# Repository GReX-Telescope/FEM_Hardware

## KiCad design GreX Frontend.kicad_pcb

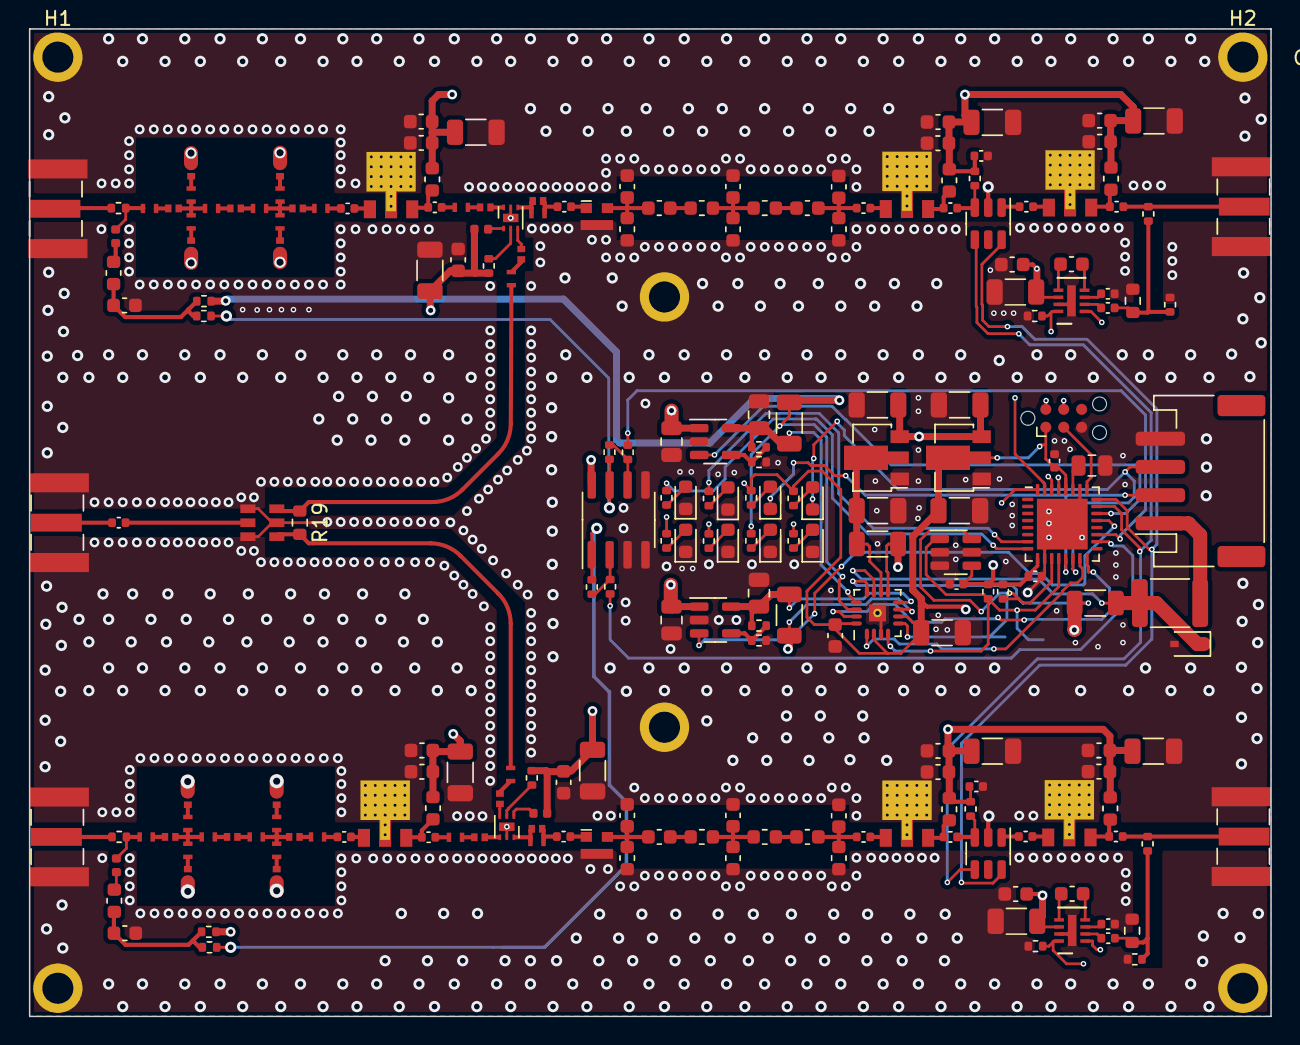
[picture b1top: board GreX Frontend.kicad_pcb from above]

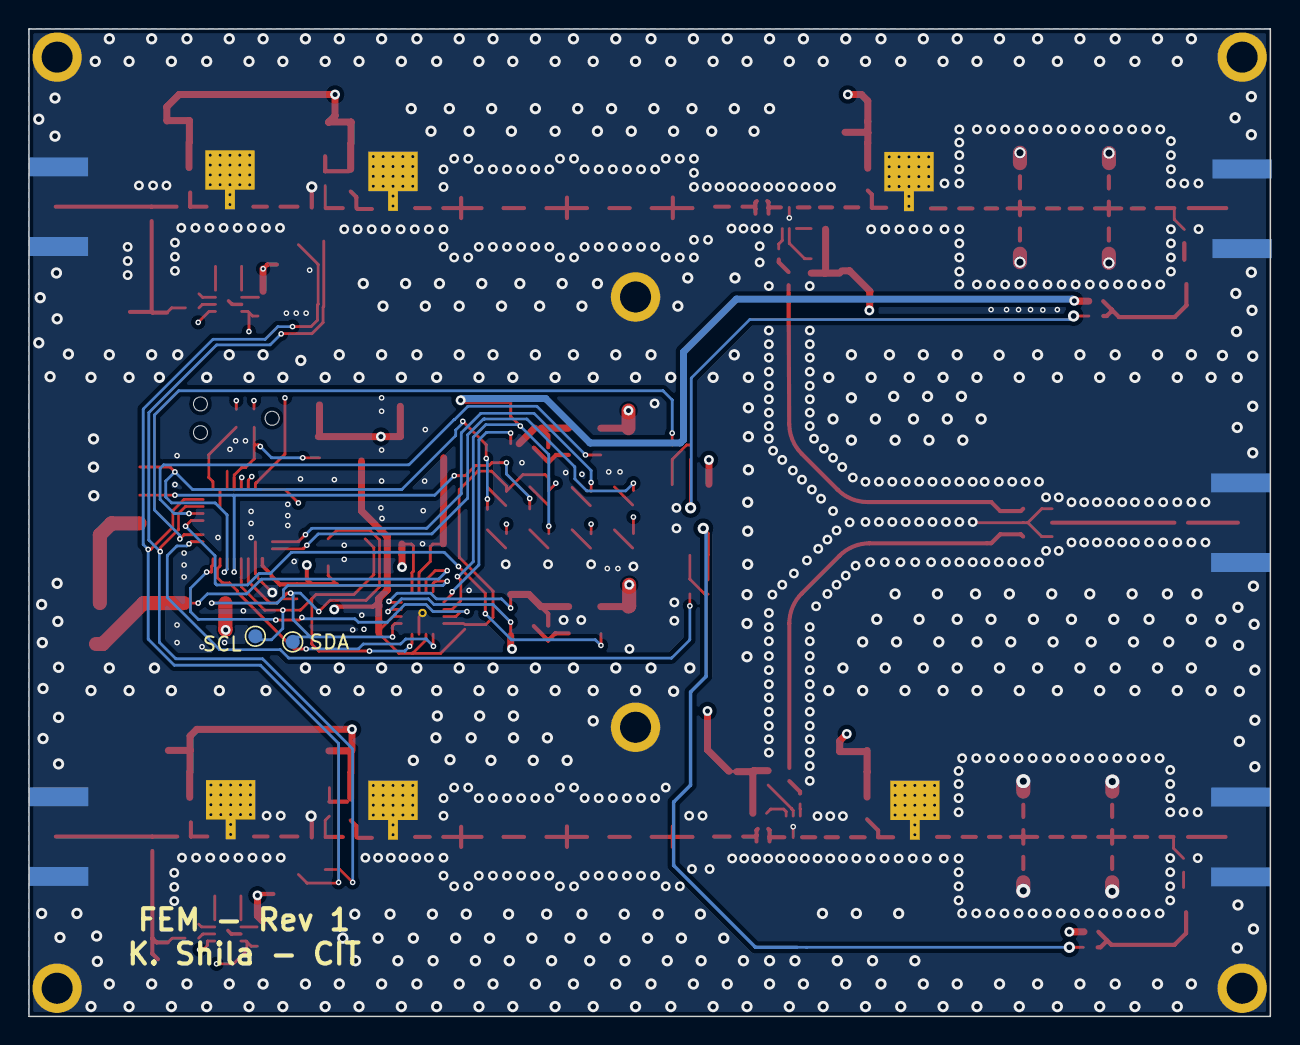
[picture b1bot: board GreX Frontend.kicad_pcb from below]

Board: 4 copper layers, 88.0 x 70.0 mm, 228 parts (2 on the bottom side), 137 nets.

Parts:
C1, C3, C15, C20, C36, C38, C43, C48: 100p; C_0603_1608Metric
C2, C16, C19, C34, C35, C44, C47, C49, C54, C63, C66: 100n; C_0402_1005Metric
C4, C7, C37, C39, C42, C56, C57, C59, C68, C69, C95, C96, C99: 100p; C_0402_1005Metric
C5, C17, C22, C32, C40, C45, C51, C52, C64, C93, C98: 1n; C_0603_1608Metric
C6, C18, C21, C25, C26, C27, C28, C31, C41, C46, C50, C53, C65, C94, C97: 10u; C_1206_3216Metric
C8, C14, C75, C81: 0.9p; C_0402_MDLX
C9, C12, C76, C79: 0.43p; C_0402_MDLX
C10, C13, C77, C80: 4.3p; C_0402_MDLX
C11, C78: 0.25p; C_0402_MDLX
C23, C24, C29, C30, C33: 1u; C_0805_2012Metric
C55, C67: 33n; C_0603_1608Metric
C70, C74, C82, C86: 18p; C_0603_1608Metric
C71, C73, C83, C85: 4.3p; C_0603_1608Metric
C72, C84: 33p; C_0603_1608Metric
C87, C88: 33p; C_0402_MDLX
C89, C90, C91, C92: 3.3p; C_0402_MDLX
D1, D2, D3, D4: RED; LED_0603_1608Metric
D5, D6: GREEN; LED_0603_1608Metric
D7, D8: BLUE; LED_0603_1608Metric
D9: D_Schottky; D_SOD-323
F1: Polyfuse; Fuse_1812_4532Metric
FB1, FB2: FerriteBead_Small; L_0603_1608Metric
H1, H2, H3, H4, H5, H6: MountingHole_2.2mm_M2_ISO7380_Pad
J1, J2, J5, J6, J7: Conn_Coaxial; SMA_Samtec_SMA-J-P-X-ST-EM1_EdgeMount
J3: Screw_Terminal_01x04; JST_PH_S4B-PH-SM4-TB_1x04-1MP_P2.00mm_Horizontal
J4: PROG; Tag-Connect_TC2030-IDC-NL_2x03_P1.27mm_Vertical
L2, L7: 82n; L_0402_1005Metric
L3, L8: 100n; L_0603_1608Metric
L4, L17, L25, L32: 9.9n; L_0402_MDLX
L5, L15, L26, L30: 8.2n; L_0402_MDLX
L9, L10, L18, L19: 1000n; L_0603_1608Metric
L12, L16, L27, L31: 7.1n; L_0402_MDLX
L13, L14, L28, L29: 16n; L_0402_MDLX
L20, L24, L33, L37: 9.1n; L_0603_1608Metric
L21, L23, L34, L36: 43n; L_0603_1608Metric
L22, L35: 5.6n; L_0603_1608Metric
L38, L39: 5.6n; L_0402_MDLX
L40, L41: 4.3n; L_0402_MDLX
L42, L43: 4.7n; L_0402_MDLX
L44, L45: 33n; L_0402_1005Metric
R1, R16, R26, R27, R28, R29: 0; R_0402_1005Metric
R2, R17: 33k; R_0402_1005Metric
R3, R18: 49.9; R_0603_1608Metric
R4, R5: 0.1; R_1206_3216Metric
R6, R7: 0.5; R_1206_3216Metric
R8, R9, R10, R11, R12, R13, R14, R15, R20, R21: 1k; R_0402_1005Metric
R19: 100; R_0603_1608Metric
R22, R23: 10k; R_0402_1005Metric
R24, R25: 20k; R_0402_1005Metric
R30, R32: 42.2k; R_0402_1005Metric
R31, R33: 12.4k; R_0402_1005Metric
R34, R35, R40, R41: 4.7k; R_0402_1005Metric
R36, R38: 226; R_0402_1005Metric
R37, R39: 61.9; R_0402_1005Metric
TP1, TP2: TestPoint; TestPoint_Pad_D1.0mm
U1, U5, U7, U15, U18, U20: ADL5545
U2, U3: GRF7001; DFN6-1.5mm-EP0.6x1.1
U4, U17: PAT1220-C-3DB; RF_Attenuator_Susumu_PAT1220
U6, U19: HMC291SE; SOT-23-6
U8, U21: LT5537; DFN-8-1EP_2x3mm_P0.5mm_EP0.61x2.2mm
U9: AZ1117-3.3; SOT-89-3
U10: AZ1117-5.0; SOT-89-3
U11, U12: SPX5205M5-L; SOT-23-5
U13: PAC1944; QFN-16_EP_3x3_Pitch0.5mm
U14: ATSAMD21E17L-M; QFN-32-1EP_5x5mm_P0.5mm_EP3.6x3.6mm
U16: TMP100; SOT-23-6
U24: SCN-2-11; FV1206-1
U25: RC4558; SOIC-8_3.9x4.9mm_P1.27mm

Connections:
+3V3: C2.1, C27.2, C31.2, C32.2, C34.1, C35.1, J4.1, R8.1, R14.1, R15.1, R34.1, R35.1, U9.2 (VO), U13.2 (Vdd), U13.6 (ADRSEL), U13.16 (~PWRDN), U14.9 (VDDIO/VDDANA), U14.28 (VDDIO), U16.4 (V+)
/RF/Input Stage 1/32_kHz: R20.2, R27.1, U25.7
/RF/Input Stage 1/Image Reject Filter1/1: L2.1, L4.1, R1.2
/RF/Input Stage 1/Image Reject Filter1/2: C4.1, L17.2
/RF/Input Stage 1/OUT: C7.2, L40.1
/RF/Input Stage 2/32_kHz: R21.2, R29.1, U25.1
/RF/Input Stage 2/Image Reject Filter1/1: L7.1, L25.1, R16.2
/RF/Input Stage 2/Image Reject Filter1/2: C39.1, L32.2
/RF/Input Stage 2/OUT: C42.2, L41.1
/RF/Output Stage 1/IF Filter1/In: C70.2, C71.2, L20.1, U4.2
/RF/Output Stage 1/IF Filter1/Out: C16.1, C73.1, C74.2, L24.1
/RF/Output Stage 1/In: C95.2, U4.1
/RF/Output Stage 2/IF Filter1/In: C82.2, C83.2, L33.1, U17.2
/RF/Output Stage 2/IF Filter1/Out: C44.1, C85.1, C86.2, L37.1
/RF/Output Stage 2/In: C96.2, U17.1
ALERT1: U13.1 (~ALERT), U14.15 (PA14)
ALERT2: U13.15 (~ALERT2), U14.16 (PA15)
ATTEN_V1: U6.4 (V1), U14.23 (PA24), U19.4 (V1)
ATTEN_V2: U6.6 (V2), U14.24 (PA25), U19.6 (V2)
GND: C1.1, C2.2, C3.1, C5.1, C6.1, C9.2, C10.1, C12.2, C13.1, C15.1, C17.1, C18.1, C20.1, C21.1, C22.1, C23.2, C24.2, C25.1, C26.1, C27.1, C28.1, C29.2, C30.2, C31.1, C32.1, C33.2, C34.2, C35.2, C36.1, C37.2, C38.1, C40.1, C41.1, C43.1, C45.1, C46.1, C48.1, C50.1, C51.1, C52.1, C53.1, C57.2, C64.1, C65.1, C69.2, C70.1, C72.1, C74.1, C76.2, C77.1, C79.2, C80.1, C82.1, C84.1, C86.1, C93.1, C94.1, C97.1, C98.1, C99.2, D1.1 (K), D2.1 (K), D3.1 (K), D4.1 (K), D5.1 (K), D6.1 (K), D9.2 (A), H1.1, H2.1, H3.1, H4.1, H5.1, H6.1, J1.2 (Ext), J2.2 (Ext), J3.4, J4.5, J5.2 (Ext), J6.2 (Ext), J7.2 (Ext), L20.2, L22.2, L24.2, L33.2, L35.2, L37.2, R2.2, R3.1, R17.2, R18.1, R31.2, R33.2, R37.2, R39.2, U1.2 (GND), U2.5 (GND), U2.EP (GND), U3.5 (GND), U3.EP (GND), U4.3, U5.2 (GND), U6.2 (GND), U7.2 (GND), U8.7 (GND), U8.9 (EP), U9.1 (GND), U10.1 (GND), U11.2 (GND), U12.2 (GND), U13.3 (GND), U13.17 (EP), U14.10 (GND), U14.26 (GND), U14.33 (EP), U15.2 (GND), U16.2 (GND), U16.3 (ADD1), U16.5 (ADD0), U17.3, U18.2 (GND), U19.2 (GND), U20.2 (GND), U21.7 (GND), U21.9 (EP), U24.1 (GND), U24.3 (GND), U24.5 (GND), U25.3 (+), U25.4 (V-), U25.5 (+)
unnamed: C1.2, FB1.2, R26.2, R27.2
unnamed: C4.2, U1.1
unnamed: C7.1, L3.2, U1.3
unnamed: C8.1, L4.2
unnamed: C8.2, L5.1, L12.2, L13.1
unnamed: C9.1, L5.2
unnamed: C10.2, L12.1
unnamed: C11.1, L13.2
unnamed: C11.2, L14.1
unnamed: C12.1, L15.2
unnamed: C13.2, L16.1
unnamed: C14.1, L14.2, L15.1, L16.2
unnamed: C14.2, L17.1
unnamed: C16.2, U5.1
unnamed: C19.1, L18.2, U5.3
unnamed: C19.2, R40.2, U6.3 (RF1)
unnamed: C33.1, U14.27 (VDDCORE)
unnamed: C36.2, FB2.2, R28.2, R29.2
unnamed: C39.2, U15.1
unnamed: C42.1, L8.2, U15.3
unnamed: C44.2, U18.1
unnamed: C47.1, L9.2, U18.3
unnamed: C47.2, R41.2, U19.3 (RF1)
unnamed: C49.1, U19.1 (RF2)
unnamed: C49.2, U20.1
unnamed: C54.1, L10.2, U20.3
unnamed: C54.2, J6.1 (In), R38.1
unnamed: C55.1, U21.5 (CAP-)
unnamed: C55.2, U21.4 (CAP+)
unnamed: C56.1, U21.2 (IN+)
unnamed: C56.2, R18.2, R38.2, R39.1
unnamed: C57.1, U21.3 (IN-)
unnamed: C59.1, J7.1 (In)
unnamed: C59.2, U24.2 (IN)
unnamed: C63.1, U6.1 (RF2)
unnamed: C63.2, U7.1
unnamed: C66.1, L19.2, U7.3
unnamed: C66.2, J2.1 (In), R36.1
unnamed: C67.1, U8.5 (CAP-)
unnamed: C67.2, U8.4 (CAP+)
unnamed: C68.1, U8.2 (IN+)
unnamed: C68.2, R3.2, R36.2, R37.1
unnamed: C69.1, U8.3 (IN-)
unnamed: C71.1, L21.1
unnamed: C72.2, L21.2, L22.1, L23.1
unnamed: C73.2, L23.2
unnamed: C75.1, L25.2
unnamed: C75.2, L26.1, L27.2, L28.1
unnamed: C76.1, L26.2
unnamed: C77.2, L27.1
unnamed: C78.1, L28.2
unnamed: C78.2, L29.1
unnamed: C79.1, L30.2
unnamed: C80.2, L31.1
unnamed: C81.1, L29.2, L30.1, L31.2
unnamed: C81.2, L32.1
unnamed: C83.1, L34.1
unnamed: C84.2, L34.2, L35.1, L36.1
unnamed: C85.2, L36.2
unnamed: C87.1, L38.2
unnamed: C87.2, U2.3 (LO)
unnamed: C88.1, L39.2
unnamed: C88.2, U3.3 (LO)
unnamed: C89.1, L40.2
unnamed: C89.2, U2.6 (RF/IF)
unnamed: C90.1, L41.2
unnamed: C90.2, U3.4 (RF/IF)
unnamed: C91.1, L42.1, U2.4 (RF/IF)
unnamed: C91.2, C95.1, L42.2
unnamed: C92.1, L43.1, U3.6 (RF/IF)
unnamed: C92.2, C96.1, L43.2
unnamed: D1.2 (A), R8.2
unnamed: D2.2 (A), R9.2
unnamed: D3.2 (A), R10.2
unnamed: D4.2 (A), R11.2
unnamed: D5.2 (A), R12.2
unnamed: D6.2 (A), R13.2
unnamed: D7.2 (A), R14.2
unnamed: D8.2 (A), R15.2
unnamed: F1.1, J3.1
unnamed: FB1.1, L2.2
unnamed: FB2.1, L7.2
unnamed: J1.1 (In), R1.1
unnamed: J5.1 (In), R16.1
unnamed: L38.1, R19.1, U24.6 (OUT_1)
unnamed: L39.1, R19.2, U24.4 (OUT_2)
unnamed: L44.1, U2.1 (VDD)
unnamed: L45.1, U3.1 (VDD)
unnamed: R20.1, R22.2, U25.6 (-)
unnamed: R21.1, R23.2, U25.2 (-)
unnamed: R24.1, U2.2 (V_EN)
unnamed: R25.2, U3.2 (V_EN)
unnamed: R30.2, R31.1, U11.4 (ADJ)
unnamed: R32.2, R33.1, U12.4 (ADJ)
RF1_32kHz: R22.1, U14.19 (PA18)
RF1_IF_POW: R2.1, U8.8 (OUT), U14.31 (PB02)
RF1_LNA_EN: U11.3 (EN), U14.22 (PA23)
RF1_STATUS_LED: R12.1, U14.8 (PA07)
RF2_32kHz: R23.1, U14.18 (PA17)
RF2_IF_POW: R17.1, U14.32 (PB03), U21.8 (OUT)
RF2_LNA_EN: U12.3 (EN), U14.21 (PA22)
RF2_STATUS_LED: R13.1, U14.7 (PA06)
RXD: D8.1 (K), J3.3, U14.14 (PA11)
SCL: R35.2, TP2.1, U13.4 (SCL), U14.12 (PA09), U16.1 (SCL)
SDA: R34.2, TP1.1, U13.5 (SDA), U14.11 (PA08), U16.6 (SDA)
SWCLK: J4.4, U14.29 (PA30)
SWDIO: J4.2, U14.30 (PA31)
TXD: D7.1 (K), J3.2, U14.13 (PA10)
VA_+: C28.2, R5.1, U10.2 (VO), U13.10 (SENSE4+)
VA_-: C3.2, C5.2, C6.2, C15.2, C17.2, C18.2, C20.2, C21.2, C22.2, C37.1, C38.2, C40.2, C41.2, C43.2, C45.2, C46.2, C48.2, C50.2, C51.2, C52.2, C53.2, C64.2, C65.2, C93.2, C94.2, C97.2, C98.2, C99.1, L3.1, L8.1, L9.1, L10.1, L18.1, L19.1, L44.2, L45.2, R5.2, R9.1, R24.2, R25.1, R40.1, R41.1, U8.1 (ENBL), U8.6 (VCC), U13.9 (SENSE4-), U21.1 (ENBL), U21.6 (VCC), U25.8 (V+)
VIN_+: D9.1 (K), F1.2, R4.1, U13.11 (SENSE1+)
VIN_-: C23.1, C24.1, C25.2, C26.2, R4.2, U9.3 (VI), U10.3 (VI), U11.1 (IN), U12.1 (IN), U13.12 (SENSE1-)
VLNA1_+: C29.1, R6.1, R30.1, U11.5 (OUT), U13.13 (SENSE2+)
VLNA1_-: R6.2, R10.1, R26.1, U13.14 (SENSE2-)
VLNA2_+: C30.1, R7.1, R32.1, U12.5 (OUT), U13.8 (SENSE3+)
VLNA2_-: R7.2, R11.1, R28.1, U13.7 (SENSE3-)
nRESET: J4.3, U14.25 (~RESET)
